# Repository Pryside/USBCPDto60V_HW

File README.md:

# USBCPDto60V_HW
the hardware portion of the USBC-PD Project

Software here: https://github.com/Pryside/USBCPDto60V

KiCad Project Files

Note: This is just a development Board, not the finished product. For testing purposes.

Done:
- ADC Voltage Measurement
- ADC Bi-Dir Current Measurement
- HRTimer D
- HRTimer C
- Full Bi-Directional Converter

To Do:
- Lower Noise on ADCs
- double check new Timer Routing
- Update ADC channel inputs

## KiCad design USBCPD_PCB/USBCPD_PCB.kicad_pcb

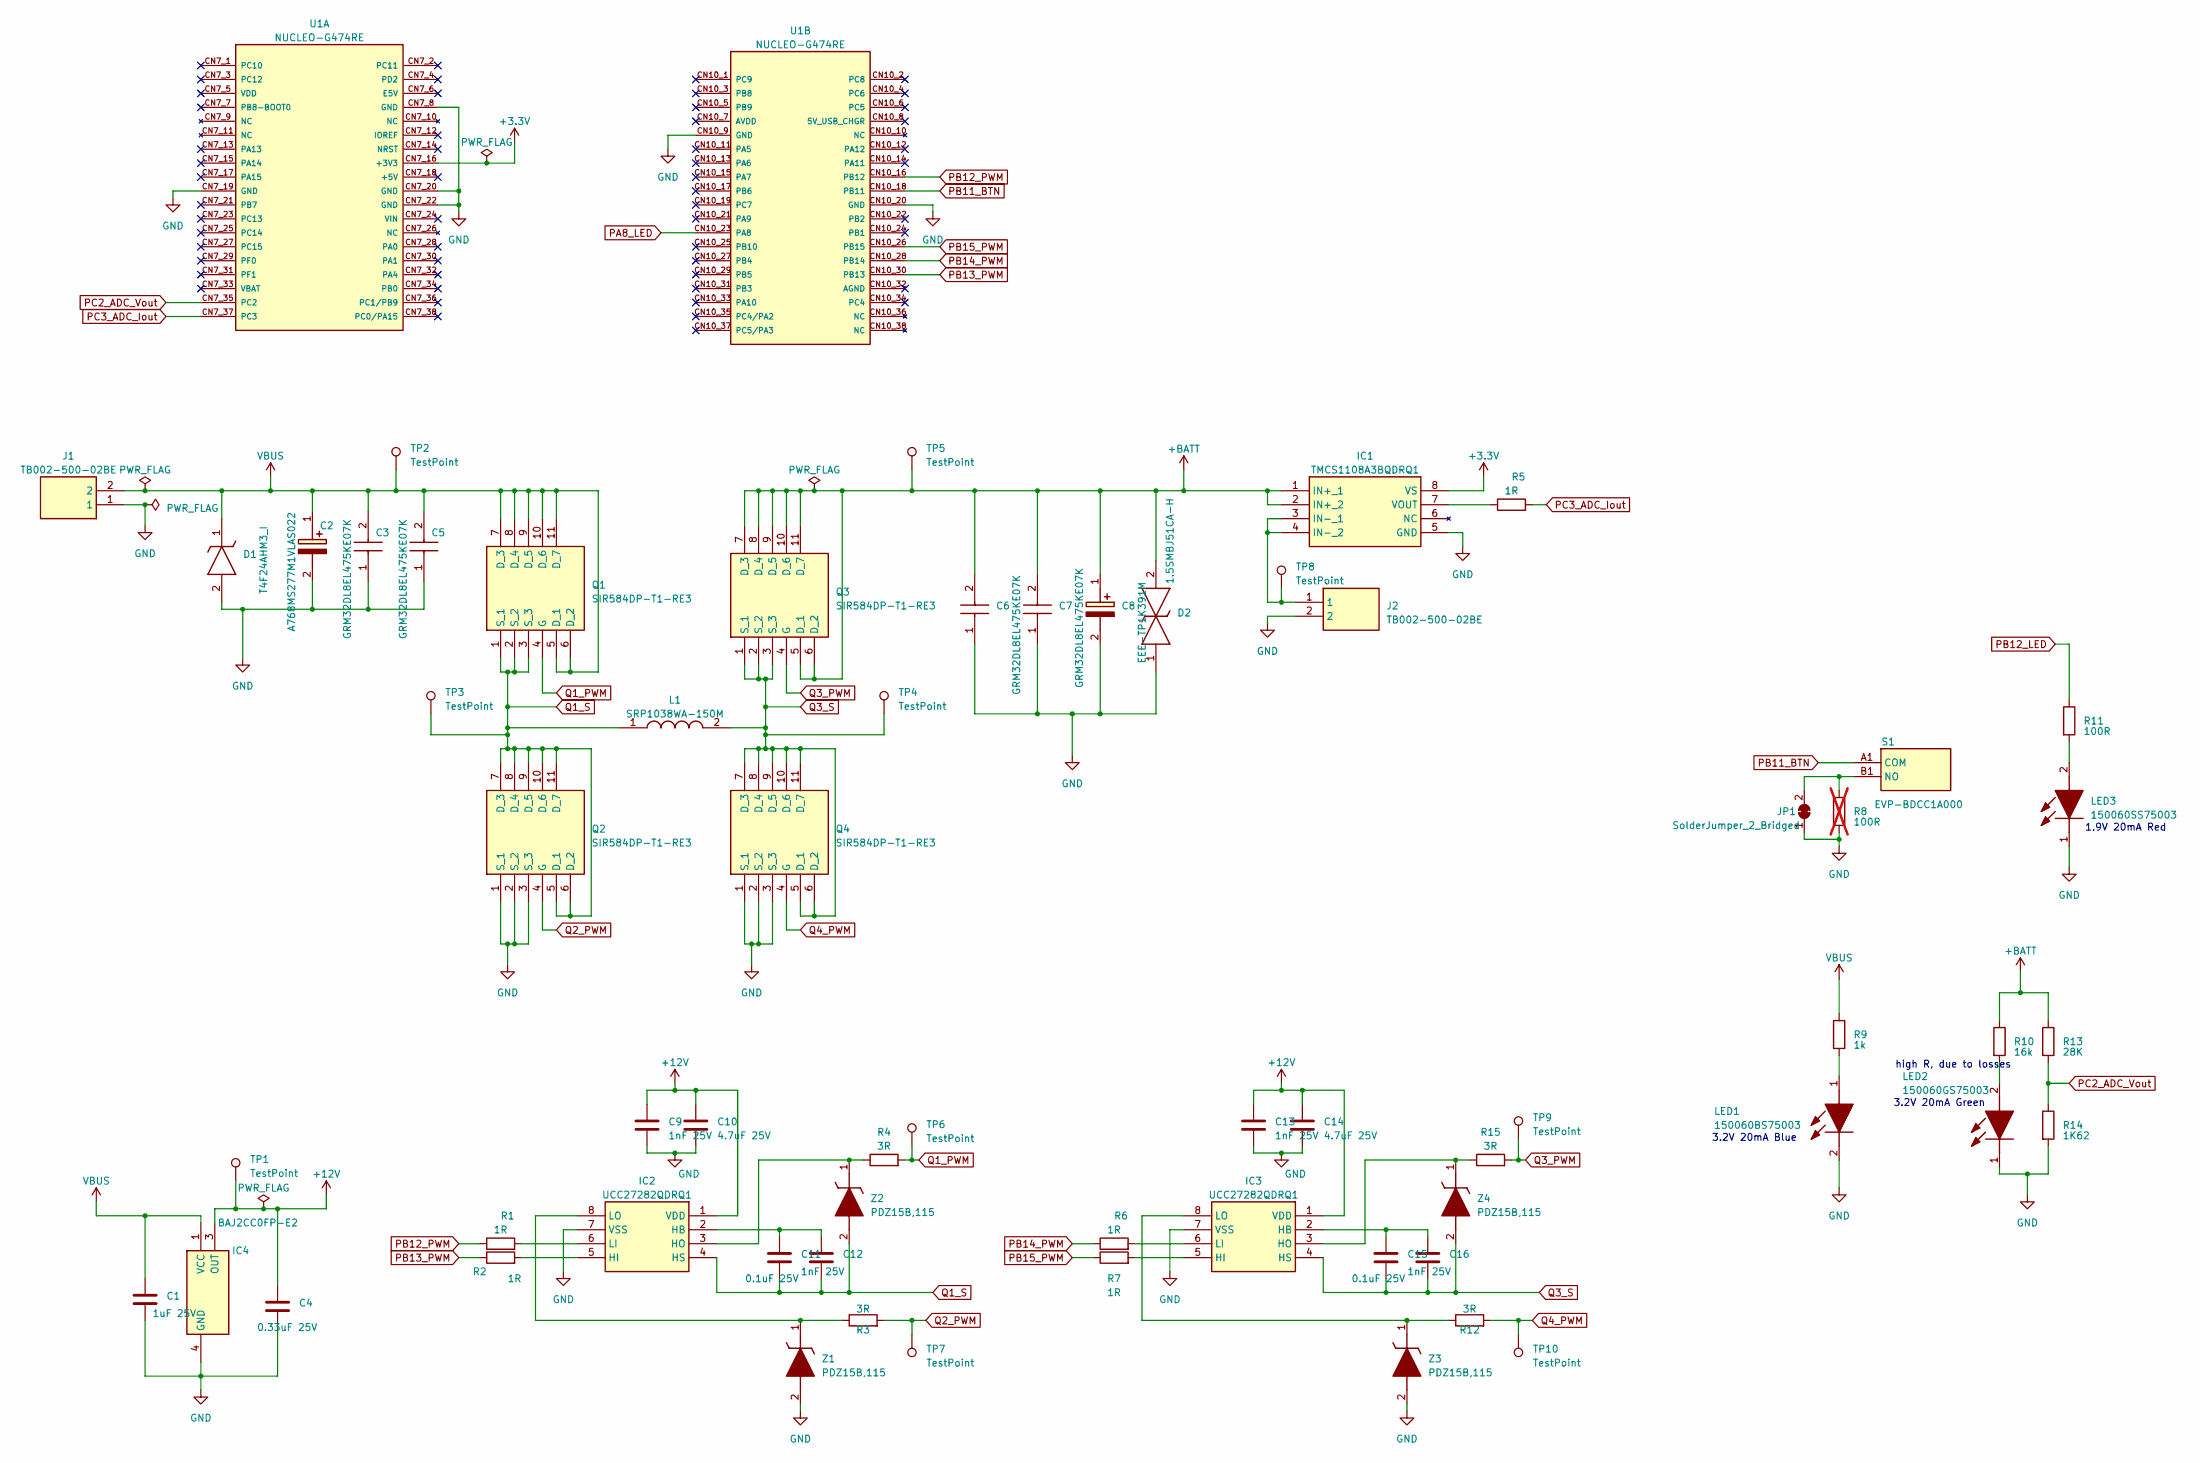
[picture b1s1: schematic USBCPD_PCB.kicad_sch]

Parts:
C1: 1uF 25V; C_0603_1608Metric_Pad1.08x0.95mm_HandSolder
C2: A768MS277M1VLAS022; CAPAE1030X1270N; Mouser Part Number 80-A768MS277M1VLAS22
C3, C5, C6, C7: GRM32DL8EL475KE07K; CAPC3225X220N; Mouser Part Number 81-GRM3DL8EL475KE07K
C4: 0.33uF 25V; C_0603_1608Metric_Pad1.08x0.95mm_HandSolder
C8: EEE-TP1K391M; EEEFK0J682AM; Mouser Part Number 667-EEE-TP1K391M
C9, C12, C13, C16: 1nF 25V; C_0402_1005Metric_Pad0.74x0.62mm_HandSolder
C10, C14: 4.7uF 25V; C_0603_1608Metric_Pad1.08x0.95mm_HandSolder
C11, C15: 0.1uF 25V; C_0603_1608Metric_Pad1.08x0.95mm_HandSolder
D1: T4F24AHM3_I; SODFL3718X108N; Manufacturer_Part_Number T4F24AHM3/I
D2: 1.5SMBJ51CA-H; DIONM5436X244N; Mouser Part Number 652-1.5SMBJ51CA-H
IC1: TMCS1108A3BQDRQ1; SOIC127P600X175-8N; Manufacturer_Part_Number TMCS1108A4BQDRQ1
IC2, IC3: UCC27282QDRQ1; SOIC127P600X175-8N; Mouser Part Number 595-UCC27282QDRQ1
IC4: BAJ2CC0FP-E2; BD750L5FPCE2; Mouser Part Number 755-BAJ2CC0FP-E2
J1, J2: TB002-500-02BE; TB00250002BE; Mouser Part Number 490-TB002-500-02BE
JP1: SolderJumper_2_Bridged; SolderJumper-2_P1.3mm_Bridged_RoundedPad1.0x1.5mm
L1: SRP1038WA-150M; SRP1038WA150M; Mouser Part Number 652-SRP1038WA-150M
LED1: 150060BS75003; Mouser Part Number 710-150060BS75003
LED2: 150060GS75003; LEDC1608X80N; Mouser Part Number 710-150060GS75003
LED3: 150060SS75003; Mouser Part Number 710-150060SS75003
Q1, Q2, Q3, Q4: SIR584DP-T1-RE3; SIR584DPT1RE3; Mouser Part Number 625-SIR582DP-T1-RE3
R1, R2, R5, R6, R7: 1R; R_0603_1608Metric_Pad0.98x0.95mm_HandSolder
R3, R4, R12, R15: 3R; R_0603_1608Metric_Pad0.98x0.95mm_HandSolder
R8: 100R; R_0603_1608Metric_Pad0.98x0.95mm_HandSolder; not fitted
R9: 1k; R_0603_1608Metric_Pad0.98x0.95mm_HandSolder
R10: 16k; R_0603_1608Metric_Pad0.98x0.95mm_HandSolder
R11: 100R; R_0603_1608Metric_Pad0.98x0.95mm_HandSolder
R13: 28K; R_0603_1608Metric_Pad0.98x0.95mm_HandSolder
R14: 1K62; R_0603_1608Metric_Pad0.98x0.95mm_HandSolder
S1: EVP-BDCC1A000; EVPBDCC1A000; Mouser Part Number 667-EVP-BDCC1A000
TP1, TP2, TP3, TP4, TP5, TP6, TP7, TP8, TP9, TP10: TestPoint; TestPoint_Pad_D1.0mm
U1: NUCLEO-G474RE; ST_NUCLEO-G474RE; PARTREV 13
Z1, Z2, Z3, Z4: PDZ15B,115; SOD2512X110N; Mouser Part Number 771-PDZ15B-T/R

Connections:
+3.3V: IC1.8 (VS), U1.CN7_16 (+3V3)
+12V: C4.1, C9.1, C10.1, C13.1, C14.1, IC2.1 (VDD), IC3.1 (VDD), IC4.3 (OUT), TP1.1
+BATT: C6.2, C7.2, C8.1 (+), D2.2, IC1.1 (IN+_1), IC1.2 (IN+_2), Q3.5 (D_1), Q3.6 (D_2), Q3.7 (D_3), Q3.8 (D_4), Q3.9 (D_5), Q3.10 (D_6), Q3.11 (D_7), R10.1, R13.1, TP5.1
GND: C1.2, C2.2 (-), C3.1, C4.2, C5.1, C6.1, C7.1, C8.2 (-), C9.2, C10.2, C13.2, C14.2, D1.2 (A), D2.1, IC1.5 (GND), IC2.7 (VSS), IC3.7 (VSS), IC4.4 (GND), J1.1, J2.2, JP1.1 (A), LED1.2 (K), LED2.1 (K), LED3.1 (K), Q2.1 (S_1), Q2.2 (S_2), Q2.3 (S_3), Q4.1 (S_1), Q4.2 (S_2), Q4.3 (S_3), R8.2, R14.2, U1.CN7_8 (GND), U1.CN7_19 (GND), U1.CN7_20 (GND), U1.CN7_22 (GND), U1.CN10_9 (GND), U1.CN10_20 (GND), Z1.2 (A), Z3.2 (A)
unnamed: IC1.3 (IN-_1), IC1.4 (IN-_2), J2.1, TP8.1
unnamed: IC1.7 (VOUT), R5.1
unnamed: C11.2, C12.1, IC2.2 (HB)
unnamed: IC2.5 (HI), R2.2
unnamed: IC2.3 (HO), R4.1, Z2.1 (K)
unnamed: IC2.6 (LI), R1.2
unnamed: IC2.8 (LO), R3.1, Z1.1 (K)
unnamed: C15.2, C16.1, IC3.2 (HB)
unnamed: IC3.5 (HI), R7.2
unnamed: IC3.3 (HO), R15.1, Z4.1 (K)
unnamed: IC3.6 (LI), R6.2
unnamed: IC3.8 (LO), R12.1, Z3.1 (K)
unnamed: JP1.2 (B), R8.1, S1.B1 (NO)
unnamed: LED1.1 (A), R9.2
unnamed: LED2.2 (A), R10.2
unnamed: LED3.2 (A), R11.2
PA8_LED: U1.CN10_23 (PA8)
PB11_BTN: S1.A1 (COM), U1.CN10_18 (PB11)
PB12_LED: R11.1
PB12_PWM: R1.1, U1.CN10_16 (PB12)
PB13_PWM: R2.1, U1.CN10_30 (PB13)
PB14_PWM: R6.1, U1.CN10_28 (PB14)
PB15_PWM: R7.1, U1.CN10_26 (PB15)
PC2_ADC_Vout: R13.2, R14.1, U1.CN7_35 (PC2)
PC3_ADC_Iout: R5.2, U1.CN7_37 (PC3)
Q1_PWM: Q1.4 (G), R4.2, TP6.1
Q1_S: C11.1, C12.2, IC2.4 (HS), L1.1, Q1.1 (S_1), Q1.2 (S_2), Q1.3 (S_3), Q2.5 (D_1), Q2.6 (D_2), Q2.7 (D_3), Q2.8 (D_4), Q2.9 (D_5), Q2.10 (D_6), Q2.11 (D_7), TP3.1, Z2.2 (A)
Q2_PWM: Q2.4 (G), R3.2, TP7.1
Q3_PWM: Q3.4 (G), R15.2, TP9.1
Q3_S: C15.1, C16.2, IC3.4 (HS), L1.2, Q3.1 (S_1), Q3.2 (S_2), Q3.3 (S_3), Q4.5 (D_1), Q4.6 (D_2), Q4.7 (D_3), Q4.8 (D_4), Q4.9 (D_5), Q4.10 (D_6), Q4.11 (D_7), TP4.1, Z4.2 (A)
Q4_PWM: Q4.4 (G), R12.2, TP10.1
VBUS: C1.1, C2.1 (+), C3.2, C5.2, D1.1 (K), IC4.1 (VCC), J1.2, Q1.5 (D_1), Q1.6 (D_2), Q1.7 (D_3), Q1.8 (D_4), Q1.9 (D_5), Q1.10 (D_6), Q1.11 (D_7), R9.1, TP2.1

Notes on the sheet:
3.2V 20mA Green
1.9V 20mA Red
high R, due to losses
3.2V 20mA Blue

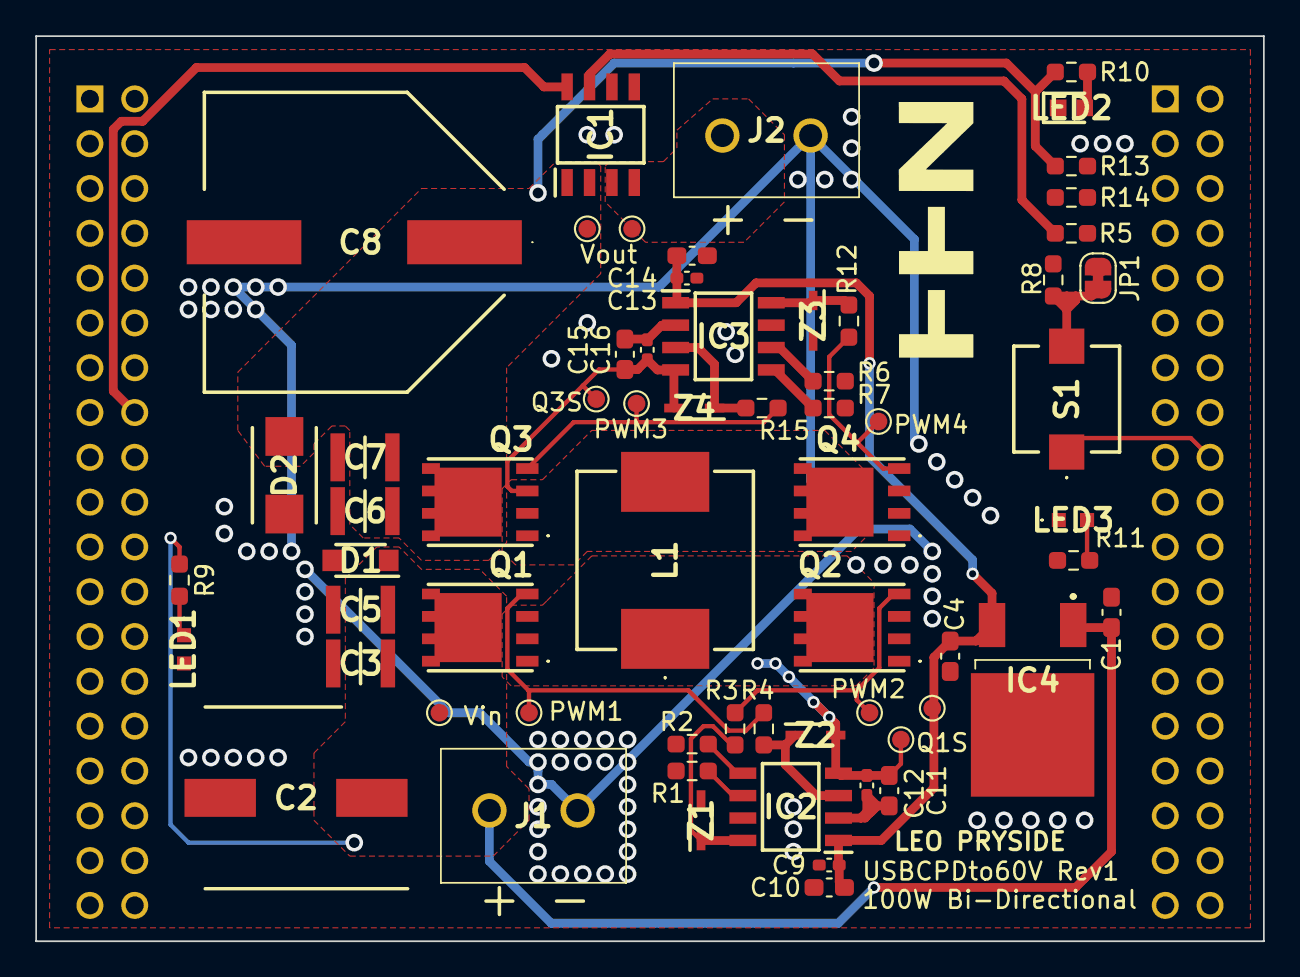
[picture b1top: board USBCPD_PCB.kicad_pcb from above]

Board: 2 copper layers, 69.6 x 51.3 mm, 64 parts (0 on the bottom side), 34 nets.

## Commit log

2023-05-21 library buildup
2023-05-22 quick library commit
2023-05-23 Added new Parts
2023-05-24 gitignore backups
2023-05-25 new components added
2023-05-31 added resistors, tvs and voltage control
    also wired up first changes
2023-06-01 added additional components
2023-06-02 Added Gate Driver Circuitry
2023-06-05 finished up main schematic
    finalized wiring, added leds with resistors, fixed ERC errors
2023-06-05 PCB layout, components sorted
2023-06-06 Schematic Fixes, Routing started
    Removed big zener diodes, replaced with smaller ones
    started routing
2023-06-06 more routing
2023-06-07 libs added, routing finalized, fixed issues
    copied libs into folder, wrong wiring fixed, added test pads and silkscreen
2023-06-07 pcb design fixes
2023-06-07 drc fixes
2023-06-07 save
2023-06-10 gerber files created + small fixes
2023-06-28 tons of errors
2023-08-07 schematic rewire changes & hotfixes
2023-11-20 Update README.md
    added link
